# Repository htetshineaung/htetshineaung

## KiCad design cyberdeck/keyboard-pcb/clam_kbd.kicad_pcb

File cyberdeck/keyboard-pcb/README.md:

# Clamshell keyboard PCB (phase 2)

Our own thumb keyboard for the Pi 5 Clamshell: RP2040, 42 keys + mouse L/R (45 switches: the space bar has two) on 1.5 mm tactile
switches, a BlackBerry-style trackball breakout under a window in the board, OLED pads, battery voltage
sense. 4-layer (In1 solid GND plane,
In2 extra routing layer), 1.0 mm, 133 × 72 mm,
shaped to drop into the clamshell base under the deck.

| File | What it is |
|---|---|
| `circuit.py` | **Source of truth**: every part, value, MPN/LCSC, position and pin→net |
| `gen_sch.py` → `clam_kbd.kicad_sch` | KiCad 7 schematic (label-connected), opens in KiCad |
| `gen_pcb.py` → `clam_kbd.kicad_pcb`, `clam_kbd.dsn` | Placed PCB with nets, outline, GND pours; Specctra file for the autorouter |
| `verify_netlist.py` | Checks KiCad's exported netlist against `circuit.py`, pin by pin |
| `run_drc.py` | KiCad DRC through the pcbnew API |
| `gen_fab.py` → `fab/bom.csv`, `fab/cpl.csv` | JLCPCB assembly files (placements from `fab/routed_positions.csv`, the routed board's export) |
| `apply_tb_module.py`, `cluster_route.py`, `trim_dangling.py`, `tb_pipeline.sh` | Turn the routed rev A board into rev B (trackball breakout) without re-routing everything |
| `render/` | Top / bottom renders, schematic PDF |

```bash
python3 gen_sch.py && kicad-cli sch export netlist clam_kbd.kicad_sch -o clam_kbd.net && python3 verify_netlist.py
KICAD7_FOOTPRINT_DIR=/usr/share/kicad/footprints /usr/bin/python3 gen_pcb.py
/usr/bin/python3 run_drc.py drc.rpt
```

## Status
- Schematic: generated; KiCad netlist matches `circuit.py` on all 91 nets (0 mismatches).
- Placement: done, matched to the clamshell key mat; DRC clean apart from unrouted nets and
  cosmetic silkscreen overlaps.
- **Routing:** scripted pipeline, run with KiCad 10's Python on the Mac (KiCad 7 works too):
  1. `route_matrix.py clam_kbd.kicad_pcb clam_kbd_rN.kicad_pcb x.dsn`: clears old routing and
     pre-routes the regular key matrix (columns on top, rows on the bottom, locked).
  2. `stitch_gnd.py clam_kbd_rN.kicad_pcb clam_kbd_rN.kicad_pcb x.dsn`: one via per small-part
     GND pad, a 3x3 via grid in the RP2040 exposed pad, and the TESTEN stub.
  3. (the DSN written by step 2 is the autorouter input; `export_dsn.py` can hide the pours)
  4. `java -Djava.awt.headless=true -jar freerouting-2.5.0.jar --gui.enabled=false
     -de clam_kbd_rN.dsn -do clam_kbd_rN.ses -mp 60 -mt 6`
  5. Import the `.ses` (`pcbnew.ImportSpecctraSES`), then `stitch_gnd.py ... --grid` for a 3 mm
     stitching-via grid, then `kicad-cli pcb drc --refill-zones --save-board`.
  6. `fix_route.py board board U1.6 U1.7 --inner [--rip 0.6]`: grid router for any pins the
     autorouter leaves open (can rip up nearby tracks and reconnect them).
  7. `gnd_islands.py board.kicad_pcb` lists any ground islands; `export_jlc.sh board` gates on DRC and
     writes the Gerber zip.
  Result (rev A): 0 unconnected, 0 DRC errors, 1171 segments on F/In2/B, 215 vias.
  Rules (`clam_kbd_rN.kicad_pro`): 0.15 mm track and clearance, 0.5/0.3 mm vias, 0.3 mm to the
  edge; all within JLCPCB's standard 4-layer process (the router's few 0.09 mm neck-downs at the
  RP2040 pins are inside JLCPCB's 0.09 mm multilayer limit).
- **Trackball (rev B):** the ready-made BlackBerry-style trackball breakout (pins VCC GND BTN RHT
  LFT DWN UP WHT GRN RED BLU) sits *under* the board: its own 11-pin header is soldered through J6
  (plated holes, both boards), two M2 screws with 2.5 mm spacers (H6, H7) hold its other edge, and
  the ball comes up through a 14 × 14 mm window centred at (124, 44). The module's hall outputs and
  click go straight to the RP2040 and its RGB LED through 100 Ω R20–R22, on GPIOs chosen so the
  RP2040 pins come in the same top-to-bottom order as the header (GPIO20 click, 21 right, 22 left,
  23 down, 24 up, 27 / 28 / 29 LED G / R / B): the wires run as one straight bus. Each LED resistor
  sits level with its header pin. Either LED polarity works (the firmware picks it). WHT is not
  connected. The module runs from +3V3.
- **Rev B routing** (`tb_pipeline.sh`, on the Mac with KiCad 10): `apply_tb_module.py` removes the
  rev A hall sensors and their tracks, adds J6 / R20–R22 / H6–H7 / the window and clears copper they
  clash with (pad nets are checked against the generated board by hash); `fix_route.py` routes the
  new connections; `cluster_route.py` redoes the RP2040's right-side fan-out (pins 34–41 all need
  an escape now), trying routing orders until every pin gets out; `trim_dangling.py` cuts the
  stubs left over. Result: 0 unconnected, 0 DRC errors.

## Circuit
- **MCU:** RP2040 + W25Q16JVSSIQ 2 MB QSPI flash, 12 MHz ABM8-272-T3 crystal (15 pF, 1 kΩ on
  XOUT), BOOT button (QSPI_SS via 1 kΩ) and RESET, 100 nF per supply pin, 1 µF on VREG in/out.
- **Power:** +5 V from the battery step-down (J1) or the programming USB through a B5819W
  (so the Pi's 5 V never back-feeds a USB host) → AP2112K-3.3 LDO → +3V3 → RP2040 core LDO → +1V1.
- **Link to the Pi:** UART at 3.3 V on J1. In the clamshell the Pi's USB ports face out
  through the case wall, so the keyboard talks over the Pi 5's internal UART connector
  (`/dev/ttyAMA10`) and Linux turns key/mouse frames into a virtual keyboard and mouse.
- **Matrix:** 4 rows × 12 columns, 1N4148WS per key (cathode to row: rows driven low, columns
  pulled up). The space bar has two switches in parallel on one diode. L/R are on column 11.
- **I²C1** (GPIO18/19, 4.7 kΩ pull-ups): OLED (J2 pads).
- **Battery sense:** 100 kΩ / 33 kΩ divider + 100 nF on GPIO26 (8.4 V → 2.08 V).

| Connector | Pins | Goes to |
|---|---|---|
| J1 PI_LINK (JST-SH 4) | 1 +5V · 2 GND · 3 KB_RX · 4 KB_TX | step-down 5 V/GND; Pi 5 UART connector (Pi TX → KB_RX, Pi RX ← KB_TX, GND) |
| J5 USB_PROG (JST-SH 4) | 1 VBUS · 2 D− · 3 D+ · 4 GND | USB cable for flashing firmware (hold BOOT, tap RESET) |
| J4 VBAT (JST-SH 2) | 1 VBAT · 2 GND | 2S pack + (after the BMS) |
| J2 OLED (4 pads, 2.54 mm) | 1 GND · 2 VCC · 3 SCL · 4 SDA | 0.96" SSD1306 module, soldered flat. **Check your module's pin order** |

| RP2040 | Function | RP2040 | Function |
|---|---|---|---|
| GPIO0 / 1 | UART0 TX / RX → Pi | GPIO18 / 19 | I²C1 SDA / SCL |
| GPIO2–5 | ROW0–3 | GPIO20–24 | trackball click / right / left / down / up |
| GPIO6–17 | COL0–11 | GPIO25 | status LED |
| GPIO26 | battery sense (ADC0) | GPIO27 / 28 / 29 | trackball LED green / red / blue |

| J6 pin | 1 | 2 | 3 | 4 | 5 | 6 | 7 | 8 | 9 | 10 | 11 |
|---|---|---|---|---|---|---|---|---|---|---|---|
| Breakout | VCC | GND | BTN | RHT | LFT | DWN | UP | WHT | GRN | RED | BLU |
| Net | +3V3 | GND | TB_CLICK | TB_RIGHT | TB_LEFT | TB_DOWN | TB_UP | — | TB_LED_G | TB_LED_R | TB_LED_B |

## Before ordering
- Route, then re-run DRC and the netlist check.
- Confirm the LCSC numbers left blank (flash, crystal, JST-SH, KMR2) in JLCPCB's part search;
  JLCPCB can also match by MPN.
- Check part rotations in JLCPCB's placement preview (KiCad and JLCPCB zero-rotation
  conventions differ for some packages).
- Datasheet sites were not reachable from the build sandbox: pinouts were checked against the
  KiCad library symbols and the standard pin tables, not the PDFs.

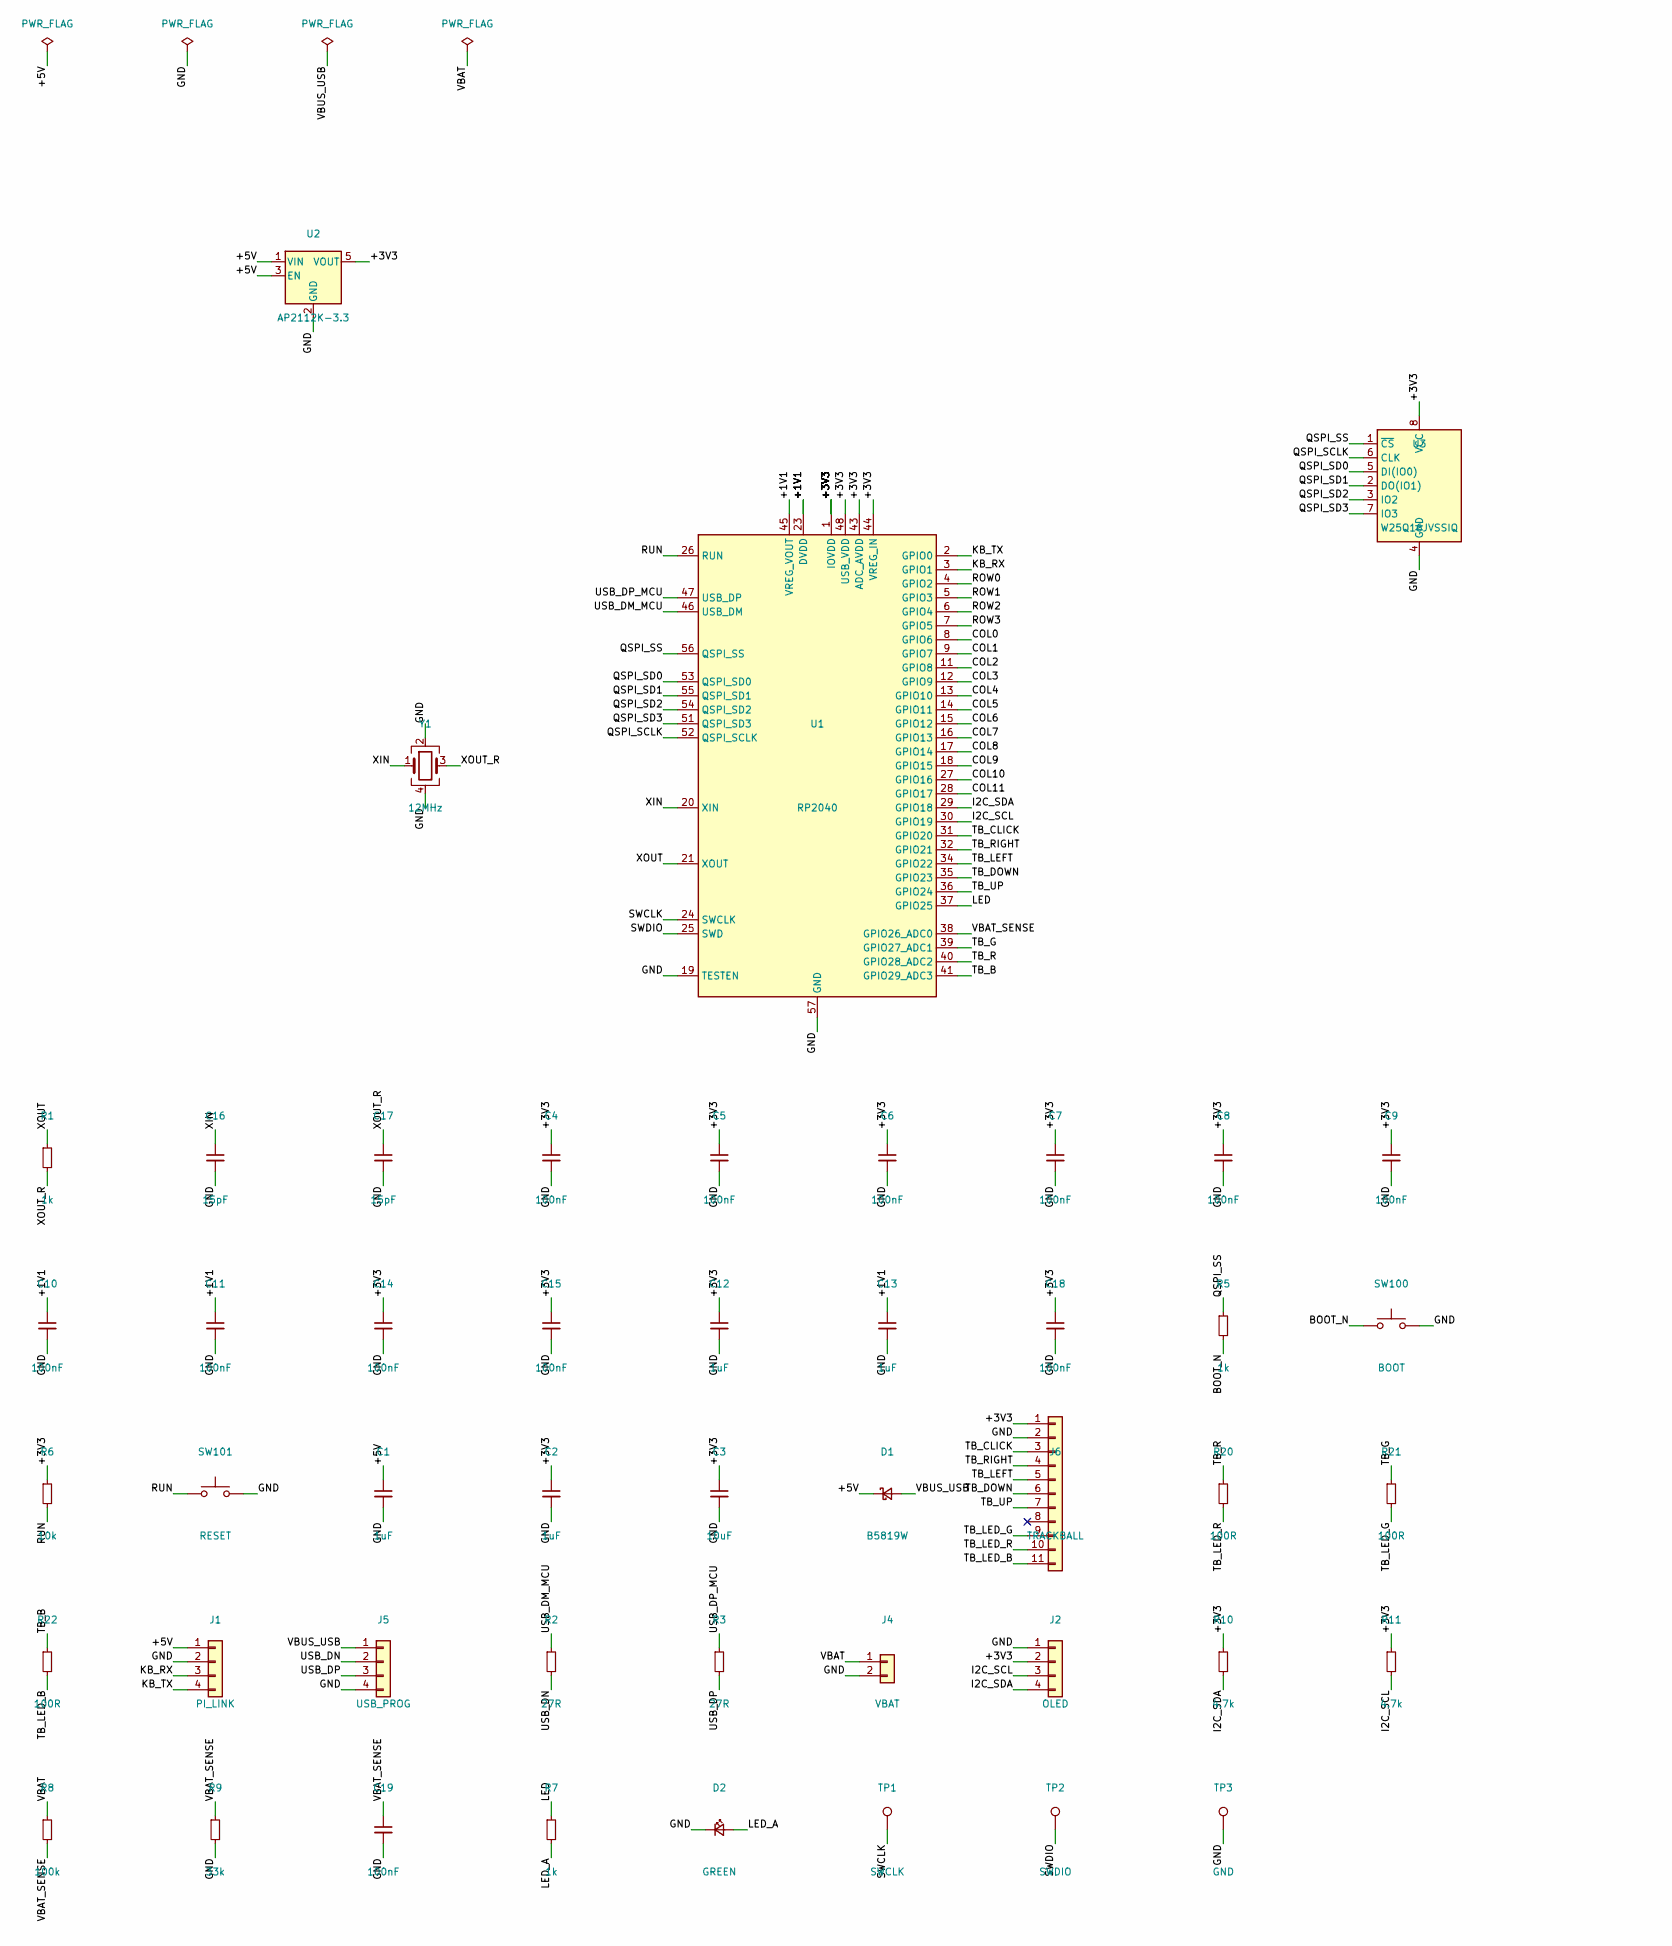
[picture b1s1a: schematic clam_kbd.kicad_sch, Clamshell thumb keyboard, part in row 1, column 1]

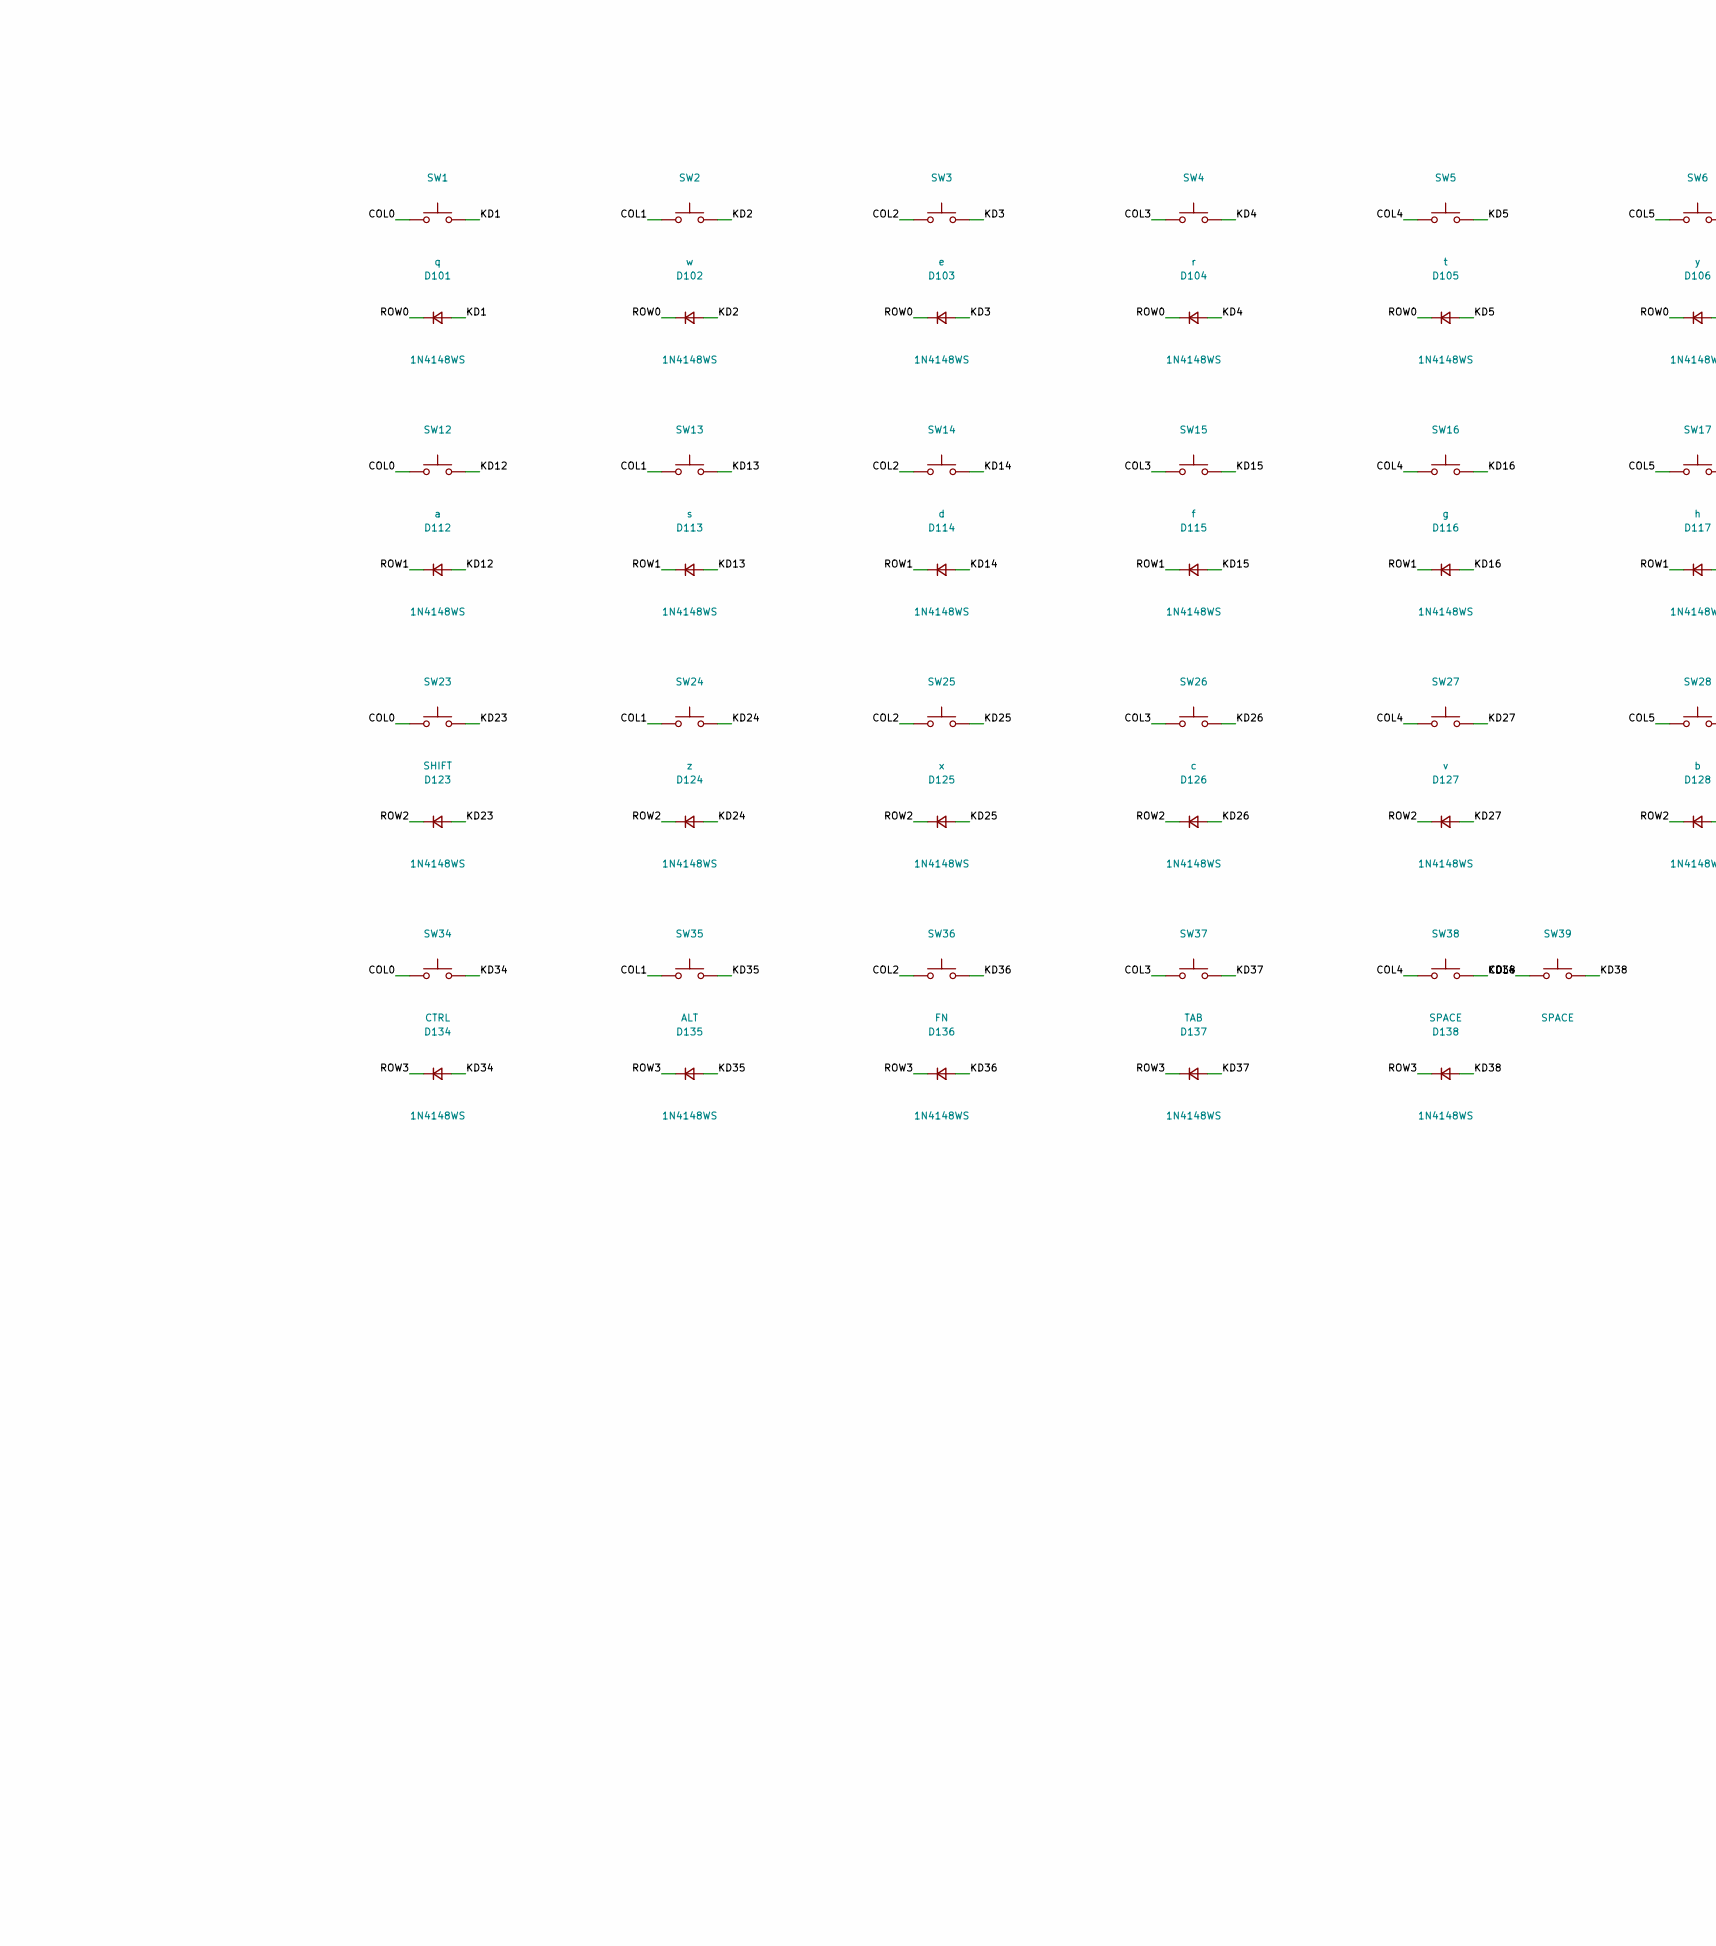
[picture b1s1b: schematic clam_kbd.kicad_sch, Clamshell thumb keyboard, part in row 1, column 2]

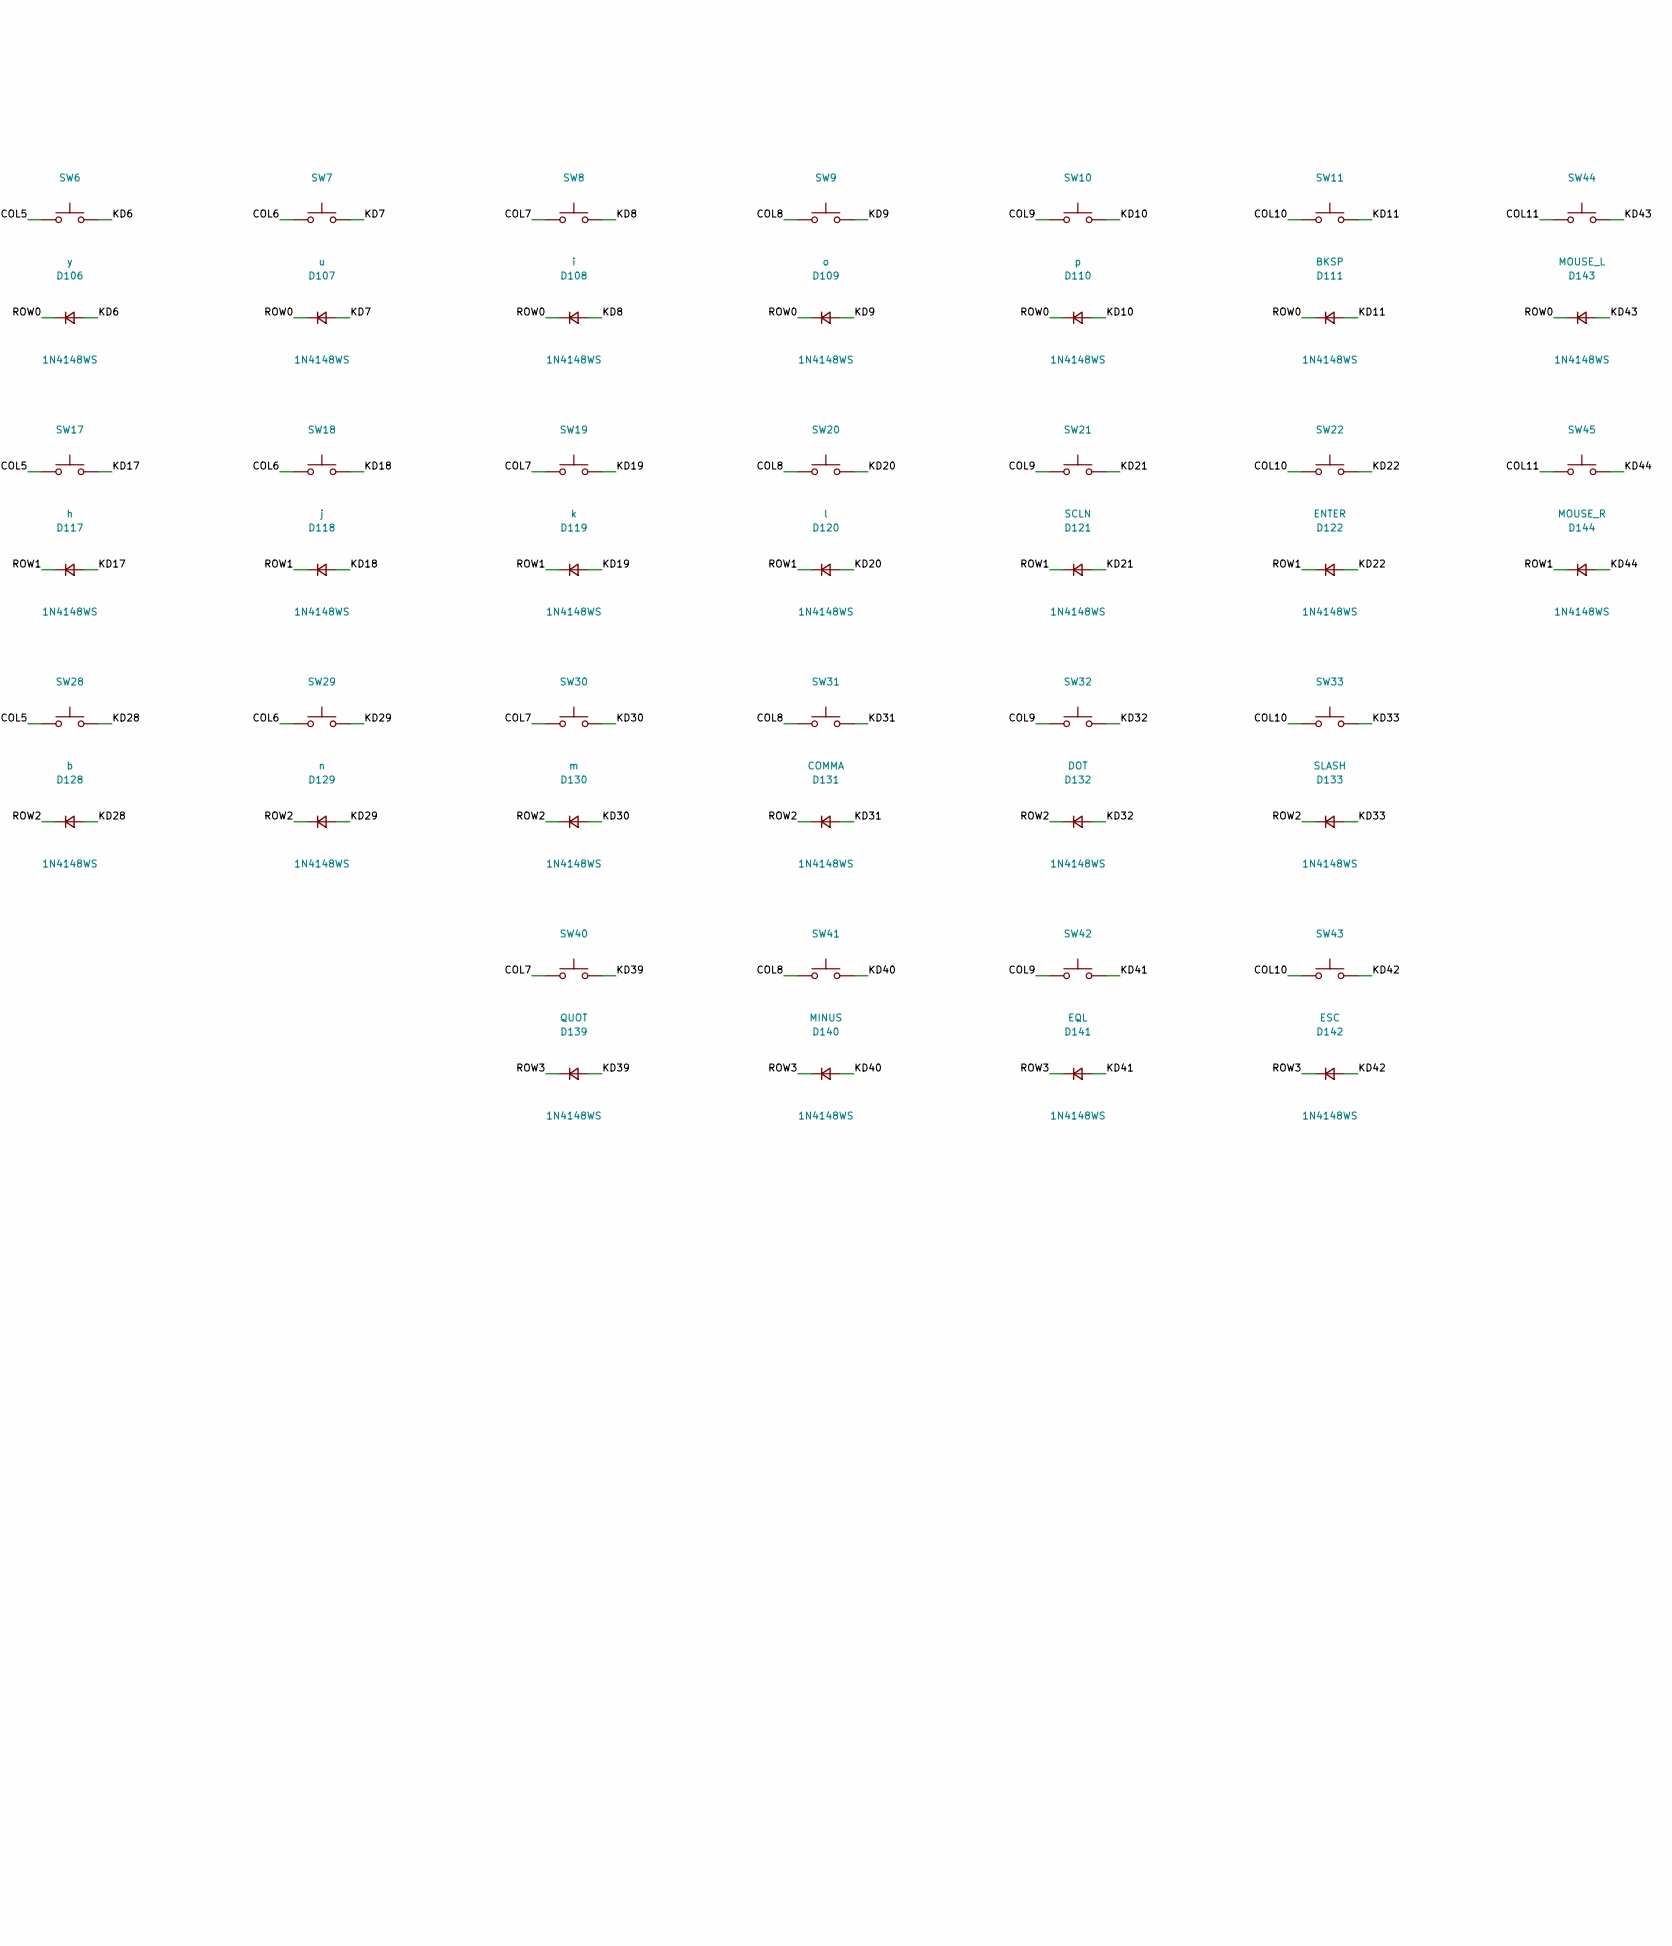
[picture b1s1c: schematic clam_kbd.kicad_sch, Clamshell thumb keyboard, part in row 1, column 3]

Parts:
C1, C2, C12, C13: 1uF; C_0402_1005Metric; MPN CL05A105KA5NQNC; LCSC C52923
C3: 10uF; C_0603_1608Metric; MPN CL10A106KP8NNNC; LCSC C19702
C4, C5, C6, C7, C8, C9, C10, C11, C14, C15, C18, C19: 100nF; C_0402_1005Metric; MPN CL05B104KO5NNNC; LCSC C1525
C16, C17: 15pF; C_0402_1005Metric; MPN 0402CG150J500NT; LCSC C1548
D1: B5819W; D_SOD-123; MPN B5819W; LCSC C8598
D2: GREEN; LED_0603_1608Metric; MPN KT-0603G; LCSC C72043
D101, D102, D103, D104, D105, D106, D107, D108, D109, D110, D111, D112, D113, D114, D115, D116, D117, D118, D119, D120, D121, D122, D123, D124, D125, D126, D127, D128, D129, D130, D131, D132, D133, D134, D135, D136, D137, D138, D139, D140, D141, D142, D143, D144: 1N4148WS; D_SOD-323; MPN 1N4148WS; LCSC C2128
J1: PI_LINK; JST_SH_SM04B-SRSS-TB_1x04-1MP_P1.00mm_Horizontal; MPN SM04B-SRSS-TB; LCSC C160404
J2: OLED; PinHeader_1x04_P2.54mm_Vertical; MPN SSD1306 0.96in 128x64 I2C module (GND V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
J4: VBAT; JST_SH_SM02B-SRSS-TB_1x02-1MP_P1.00mm_Horizontal; MPN SM02B-SRSS-TB; LCSC C160402
J5: USB_PROG; JST_SH_SM04B-SRSS-TB_1x04-1MP_P1.00mm_Horizontal; MPN SM04B-SRSS-TB; LCSC C160404
J6: TRACKBALL; PinHeader_1x11_P2.54mm_Vertical; MPN trackball breakout header (solder the m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
R1, R5, R7: 1k; R_0402_1005Metric; MPN 0402WGF1001TCE; LCSC C11702
R2, R3: 27R; R_0402_1005Metric; MPN 0402WGF270KTCE; LCSC C25100
R6: 10k; R_0402_1005Metric; MPN 0402WGF1002TCE; LCSC C25744
R8: 100k; R_0402_1005Metric; MPN 0402WGF1003TCE; LCSC C25741
R9: 33k; R_0402_1005Metric; MPN 0402WGF3302TCE; LCSC C25779
R10, R11: 4.7k; R_0402_1005Metric; MPN 0402WGF4701TCE; LCSC C25900
R20, R21, R22: 100R; R_0402_1005Metric; MPN 0402WGF1000TCE; LCSC C25076
SW1: q; SW_Push_1P1T_XKB_TS-1187A; MPN TS-1187A-B-A-B; LCSC C318884
SW2: w; SW_Push_1P1T_XKB_TS-1187A; MPN TS-1187A-B-A-B; LCSC C318884
SW3: e; SW_Push_1P1T_XKB_TS-1187A; MPN TS-1187A-B-A-B; LCSC C318884
SW4: r; SW_Push_1P1T_XKB_TS-1187A; MPN TS-1187A-B-A-B; LCSC C318884
SW5: t; SW_Push_1P1T_XKB_TS-1187A; MPN TS-1187A-B-A-B; LCSC C318884
SW6: y; SW_Push_1P1T_XKB_TS-1187A; MPN TS-1187A-B-A-B; LCSC C318884
SW7: u; SW_Push_1P1T_XKB_TS-1187A; MPN TS-1187A-B-A-B; LCSC C318884
SW8: i; SW_Push_1P1T_XKB_TS-1187A; MPN TS-1187A-B-A-B; LCSC C318884
SW9: o; SW_Push_1P1T_XKB_TS-1187A; MPN TS-1187A-B-A-B; LCSC C318884
SW10: p; SW_Push_1P1T_XKB_TS-1187A; MPN TS-1187A-B-A-B; LCSC C318884
SW11: BKSP; SW_Push_1P1T_XKB_TS-1187A; MPN TS-1187A-B-A-B; LCSC C318884
SW12: a; SW_Push_1P1T_XKB_TS-1187A; MPN TS-1187A-B-A-B; LCSC C318884
SW13: s; SW_Push_1P1T_XKB_TS-1187A; MPN TS-1187A-B-A-B; LCSC C318884
SW14: d; SW_Push_1P1T_XKB_TS-1187A; MPN TS-1187A-B-A-B; LCSC C318884
SW15: f; SW_Push_1P1T_XKB_TS-1187A; MPN TS-1187A-B-A-B; LCSC C318884
SW16: g; SW_Push_1P1T_XKB_TS-1187A; MPN TS-1187A-B-A-B; LCSC C318884
SW17: h; SW_Push_1P1T_XKB_TS-1187A; MPN TS-1187A-B-A-B; LCSC C318884
SW18: j; SW_Push_1P1T_XKB_TS-1187A; MPN TS-1187A-B-A-B; LCSC C318884
SW19: k; SW_Push_1P1T_XKB_TS-1187A; MPN TS-1187A-B-A-B; LCSC C318884
SW20: l; SW_Push_1P1T_XKB_TS-1187A; MPN TS-1187A-B-A-B; LCSC C318884
SW21: SCLN; SW_Push_1P1T_XKB_TS-1187A; MPN TS-1187A-B-A-B; LCSC C318884
SW22: ENTER; SW_Push_1P1T_XKB_TS-1187A; MPN TS-1187A-B-A-B; LCSC C318884
SW23: SHIFT; SW_Push_1P1T_XKB_TS-1187A; MPN TS-1187A-B-A-B; LCSC C318884
SW24: z; SW_Push_1P1T_XKB_TS-1187A; MPN TS-1187A-B-A-B; LCSC C318884
SW25: x; SW_Push_1P1T_XKB_TS-1187A; MPN TS-1187A-B-A-B; LCSC C318884
SW26: c; SW_Push_1P1T_XKB_TS-1187A; MPN TS-1187A-B-A-B; LCSC C318884
SW27: v; SW_Push_1P1T_XKB_TS-1187A; MPN TS-1187A-B-A-B; LCSC C318884
SW28: b; SW_Push_1P1T_XKB_TS-1187A; MPN TS-1187A-B-A-B; LCSC C318884
SW29: n; SW_Push_1P1T_XKB_TS-1187A; MPN TS-1187A-B-A-B; LCSC C318884
SW30: m; SW_Push_1P1T_XKB_TS-1187A; MPN TS-1187A-B-A-B; LCSC C318884
SW31: COMMA; SW_Push_1P1T_XKB_TS-1187A; MPN TS-1187A-B-A-B; LCSC C318884
SW32: DOT; SW_Push_1P1T_XKB_TS-1187A; MPN TS-1187A-B-A-B; LCSC C318884
SW33: SLASH; SW_Push_1P1T_XKB_TS-1187A; MPN TS-1187A-B-A-B; LCSC C318884
SW34: CTRL; SW_Push_1P1T_XKB_TS-1187A; MPN TS-1187A-B-A-B; LCSC C318884
SW35: ALT; SW_Push_1P1T_XKB_TS-1187A; MPN TS-1187A-B-A-B; LCSC C318884
SW36: FN; SW_Push_1P1T_XKB_TS-1187A; MPN TS-1187A-B-A-B; LCSC C318884
SW37: TAB; SW_Push_1P1T_XKB_TS-1187A; MPN TS-1187A-B-A-B; LCSC C318884
SW38, SW39: SPACE; SW_Push_1P1T_XKB_TS-1187A; MPN TS-1187A-B-A-B; LCSC C318884
SW40: QUOT; SW_Push_1P1T_XKB_TS-1187A; MPN TS-1187A-B-A-B; LCSC C318884
SW41: MINUS; SW_Push_1P1T_XKB_TS-1187A; MPN TS-1187A-B-A-B; LCSC C318884
SW42: EQL; SW_Push_1P1T_XKB_TS-1187A; MPN TS-1187A-B-A-B; LCSC C318884
SW43: ESC; SW_Push_1P1T_XKB_TS-1187A; MPN TS-1187A-B-A-B; LCSC C318884
SW44: MOUSE_L; SW_Push_1P1T_XKB_TS-1187A; MPN TS-1187A-B-A-B; LCSC C318884
SW45: MOUSE_R; SW_Push_1P1T_XKB_TS-1187A; MPN TS-1187A-B-A-B; LCSC C318884
SW100: BOOT; SW_Push_1P1T_NO_CK_KMR2; MPN KMR221GLFS; LCSC C72443
SW101: RESET; SW_Push_1P1T_NO_CK_KMR2; MPN KMR221GLFS; LCSC C72443
TP1: SWCLK; TestPoint_Pad_D1.0mm
TP2: SWDIO; TestPoint_Pad_D1.0mm
TP3: GND; TestPoint_Pad_D1.0mm
U1: RP2040; QFN-56-1EP_7x7mm_P0.4mm_EP3.2x3.2mm; MPN RP2040; LCSC C2040
U2: AP2112K-3.3; SOT-23-5; MPN AP2112K-3.3TRG1; LCSC C51118
U3: W25Q16JVSSIQ; SOIC-8_5.23x5.23mm_P1.27mm; MPN W25Q16JVSSIQ; LCSC C131025
Y1: 12MHz; Crystal_SMD_3225-4Pin_3.2x2.5mm; MPN ABM8-272-T3; LCSC C20625731

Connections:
+1V1: C10.1, C11.1, C13.1, U1.23 (DVDD), U1.45 (VREG_VOUT), U1.50 (DVDD)
+3V3: C2.1, C3.1, C4.1, C5.1, C6.1, C7.1, C8.1, C9.1, C12.1, C14.1, C15.1, C18.1, J2.2, J6.1, R6.1, R10.1, R11.1, U1.1 (IOVDD), U1.10 (IOVDD), U1.22 (IOVDD), U1.33 (IOVDD), U1.42 (IOVDD), U1.43 (ADC_AVDD), U1.44 (VREG_IN), U1.48 (USB_VDD), U1.49 (IOVDD), U2.5 (VOUT), U3.8 (VCC)
+5V: C1.1, D1.1 (K), J1.1, U2.1 (VIN), U2.3 (EN)
BOOT_N: R5.2, SW100.1
COL0: SW1.1, SW12.1, SW23.1, SW34.1, U1.8 (GPIO6)
COL1: SW2.1, SW13.1, SW24.1, SW35.1, U1.9 (GPIO7)
COL2: SW3.1, SW14.1, SW25.1, SW36.1, U1.11 (GPIO8)
COL3: SW4.1, SW15.1, SW26.1, SW37.1, U1.12 (GPIO9)
COL4: SW5.1, SW16.1, SW27.1, SW38.1, SW39.1, U1.13 (GPIO10)
COL5: SW6.1, SW17.1, SW28.1, U1.14 (GPIO11)
COL6: SW7.1, SW18.1, SW29.1, U1.15 (GPIO12)
COL7: SW8.1, SW19.1, SW30.1, SW40.1, U1.16 (GPIO13)
COL8: SW9.1, SW20.1, SW31.1, SW41.1, U1.17 (GPIO14)
COL9: SW10.1, SW21.1, SW32.1, SW42.1, U1.18 (GPIO15)
COL10: SW11.1, SW22.1, SW33.1, SW43.1, U1.27 (GPIO16)
COL11: SW44.1, SW45.1, U1.28 (GPIO17)
GND: C1.2, C2.2, C3.2, C4.2, C5.2, C6.2, C7.2, C8.2, C9.2, C10.2, C11.2, C12.2, C13.2, C14.2, C15.2, C16.2, C17.2, C18.2, C19.2, D2.1 (K), J1.2, J2.1, J4.2, J5.4, J6.2, R9.2, SW100.2, SW101.2, TP3.1, U1.19 (TESTEN), U1.57 (GND), U2.2 (GND), U3.4 (GND), Y1.2, Y1.4
I2C_SCL: J2.3, R11.2, U1.30 (GPIO19)
I2C_SDA: J2.4, R10.2, U1.29 (GPIO18)
KB_RX: J1.3, U1.3 (GPIO1)
KB_TX: J1.4, U1.2 (GPIO0)
KD1: D101.2 (A), SW1.2
KD2: D102.2 (A), SW2.2
KD3: D103.2 (A), SW3.2
KD4: D104.2 (A), SW4.2
KD5: D105.2 (A), SW5.2
KD6: D106.2 (A), SW6.2
KD7: D107.2 (A), SW7.2
KD8: D108.2 (A), SW8.2
KD9: D109.2 (A), SW9.2
KD10: D110.2 (A), SW10.2
KD11: D111.2 (A), SW11.2
KD12: D112.2 (A), SW12.2
KD13: D113.2 (A), SW13.2
KD14: D114.2 (A), SW14.2
KD15: D115.2 (A), SW15.2
KD16: D116.2 (A), SW16.2
KD17: D117.2 (A), SW17.2
KD18: D118.2 (A), SW18.2
KD19: D119.2 (A), SW19.2
KD20: D120.2 (A), SW20.2
KD21: D121.2 (A), SW21.2
KD22: D122.2 (A), SW22.2
KD23: D123.2 (A), SW23.2
KD24: D124.2 (A), SW24.2
KD25: D125.2 (A), SW25.2
KD26: D126.2 (A), SW26.2
KD27: D127.2 (A), SW27.2
KD28: D128.2 (A), SW28.2
KD29: D129.2 (A), SW29.2
KD30: D130.2 (A), SW30.2
KD31: D131.2 (A), SW31.2
KD32: D132.2 (A), SW32.2
KD33: D133.2 (A), SW33.2
KD34: D134.2 (A), SW34.2
KD35: D135.2 (A), SW35.2
KD36: D136.2 (A), SW36.2
KD37: D137.2 (A), SW37.2
KD38: D138.2 (A), SW38.2, SW39.2
KD39: D139.2 (A), SW40.2
KD40: D140.2 (A), SW41.2
KD41: D141.2 (A), SW42.2
KD42: D142.2 (A), SW43.2
KD43: D143.2 (A), SW44.2
KD44: D144.2 (A), SW45.2
LED: R7.1, U1.37 (GPIO25)
LED_A: D2.2 (A), R7.2
QSPI_SCLK: U1.52 (QSPI_SCLK), U3.6 (CLK)
QSPI_SD0: U1.53 (QSPI_SD0), U3.5 (DI(IO0))
QSPI_SD1: U1.55 (QSPI_SD1), U3.2 (DO(IO1))
QSPI_SD2: U1.54 (QSPI_SD2), U3.3 (IO2)
QSPI_SD3: U1.51 (QSPI_SD3), U3.7 (IO3)
QSPI_SS: R5.1, U1.56 (QSPI_SS), U3.1 (~CS)
ROW0: D101.1 (K), D102.1 (K), D103.1 (K), D104.1 (K), D105.1 (K), D106.1 (K), D107.1 (K), D108.1 (K), D109.1 (K), D110.1 (K), D111.1 (K), D143.1 (K), U1.4 (GPIO2)
ROW1: D112.1 (K), D113.1 (K), D114.1 (K), D115.1 (K), D116.1 (K), D117.1 (K), D118.1 (K), D119.1 (K), D120.1 (K), D121.1 (K), D122.1 (K), D144.1 (K), U1.5 (GPIO3)
ROW2: D123.1 (K), D124.1 (K), D125.1 (K), D126.1 (K), D127.1 (K), D128.1 (K), D129.1 (K), D130.1 (K), D131.1 (K), D132.1 (K), D133.1 (K), U1.6 (GPIO4)
ROW3: D134.1 (K), D135.1 (K), D136.1 (K), D137.1 (K), D138.1 (K), D139.1 (K), D140.1 (K), D141.1 (K), D142.1 (K), U1.7 (GPIO5)
RUN: R6.2, SW101.1, U1.26 (RUN)
SWCLK: TP1.1, U1.24 (SWCLK)
SWDIO: TP2.1, U1.25 (SWD)
TB_B: R22.1, U1.41 (GPIO29_ADC3)
TB_CLICK: J6.3, U1.31 (GPIO20)
TB_DOWN: J6.6, U1.35 (GPIO23)
TB_G: R21.1, U1.39 (GPIO27_ADC1)
TB_LED_B: J6.11, R22.2
TB_LED_G: J6.9, R21.2
TB_LED_R: J6.10, R20.2
TB_LEFT: J6.5, U1.34 (GPIO22)
TB_R: R20.1, U1.40 (GPIO28_ADC2)
TB_RIGHT: J6.4, U1.32 (GPIO21)
TB_UP: J6.7, U1.36 (GPIO24)
USB_DM_MCU: R2.1, U1.46 (USB_DM)
USB_DN: J5.2, R2.2
USB_DP: J5.3, R3.2
USB_DP_MCU: R3.1, U1.47 (USB_DP)
VBAT: J4.1, R8.1
VBAT_SENSE: C19.1, R8.2, R9.1, U1.38 (GPIO26_ADC0)
VBUS_USB: D1.2 (A), J5.1
XIN: C16.1, U1.20 (XIN), Y1.1
XOUT: R1.1, U1.21 (XOUT)
XOUT_R: C17.1, R1.2, Y1.3

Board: 4 copper layers, 144 parts (86 on the bottom side), 101 nets, no tracks yet.

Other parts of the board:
H1, H2, H3, H4, H5, H6, H7: MountingHole_2.2mm_M2

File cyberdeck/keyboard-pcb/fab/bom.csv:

Comment,Designator,Footprint,LCSC,MPN,Qty
Key switch 5.1x5.1x1.5,"SW1,SW2,SW3,SW4,SW5,SW6,SW7,SW8,SW9,SW10,SW11,SW12,SW13,SW14,SW15,SW16,SW17,SW18,SW19,SW20,SW21,SW22,SW23,SW24,SW25,SW26,SW27,SW28,SW29,SW30,SW31,SW32,SW33,SW34,SW35,SW36,SW37,SW38,SW39,SW40,SW41,SW42,SW43,SW44,SW45",SW_Push_1P1T_XKB_TS-1187A,C318884,TS-1187A-B-A-B,45
BOOT,SW100,SW_Push_1P1T_NO_CK_KMR2,C72443,KMR221GLFS,1
RESET,SW101,SW_Push_1P1T_NO_CK_KMR2,C72443,KMR221GLFS,1
1k,"R1,R5,R7",R_0402_1005Metric,C11702,0402WGF1001TCE,3
GREEN,D2,LED_0603_1608Metric,C72043,KT-0603G,1
100nF,"C4,C5,C6,C7,C8,C9,C10,C11,C14,C15,C18,C19",C_0402_1005Metric,C1525,CL05B104KO5NNNC,12
1N4148WS,"D101,D102,D103,D104,D105,D106,D107,D108,D109,D110,D111,D112,D113,D114,D115,D116,D117,D118,D119,D120,D121,D122,D123,D124,D125,D126,D127,D128,D129,D130,D131,D132,D133,D134,D135,D136,D137,D138,D139,D140,D141,D142,D143,D144",D_SOD-323,C2128,1N4148WS,44
AP2112K-3.3,U2,SOT-23-5,C51118,AP2112K-3.3TRG1,1
100R,"R20,R21,R22",R_0402_1005Metric,C25076,0402WGF1000TCE,3
USB_PROG,J5,JST_SH_SM04B-SRSS-TB_1x04-1MP_P1.00mm_Horizontal,C160404,SM04B-SRSS-TB,1
100k,R8,R_0402_1005Metric,C25741,0402WGF1003TCE,1
4.7k,"R10,R11",R_0402_1005Metric,C25900,0402WGF4701TCE,2
PI_LINK,J1,JST_SH_SM04B-SRSS-TB_1x04-1MP_P1.00mm_Horizontal,C160404,SM04B-SRSS-TB,1
33k,R9,R_0402_1005Metric,C25779,0402WGF3302TCE,1
1uF,"C1,C2,C12,C13",C_0402_1005Metric,C52923,CL05A105KA5NQNC,4
27R,"R2,R3",R_0402_1005Metric,C25100,0402WGF270KTCE,2
12MHz,Y1,Crystal_SMD_3225-4Pin_3.2x2.5mm,C20625731,ABM8-272-T3,1
B5819W,D1,D_SOD-123,C8598,B5819W,1
10k,R6,R_0402_1005Metric,C25744,0402WGF1002TCE,1
RP2040,U1,QFN-56-1EP_7x7mm_P0.4mm_EP3.2x3.2mm,C2040,RP2040,1
W25Q16JVSSIQ,U3,SOIC-8_5.23x5.23mm_P1.27mm,C131025,W25Q16JVSSIQ,1
15pF,"C16,C17",C_0402_1005Metric,C1548,0402CG150J500NT,2
10uF,C3,C_0603_1608Metric,C19702,CL10A106KP8NNNC,1
VBAT,J4,JST_SH_SM02B-SRSS-TB_1x02-1MP_P1.00mm_Horizontal,C160402,SM02B-SRSS-TB,1

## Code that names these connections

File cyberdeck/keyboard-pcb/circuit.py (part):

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      "24": "SWCLK", "25": "SWDIO", "26": "RUN",
      "46": "USB_DM_MCU", "47": "USB_DP_MCU",
      "51": "QSPI_SD3", "52": "QSPI_SCLK", "53": "QSPI_SD0", "54": "QSPI_SD2", "55": "QSPI_SD1", "56": "QSPI_SS",
      "2": "KB_TX", "3": "KB_RX",                       # GPIO0/1 = UART0 TX/RX -> Pi
      "4": "ROW0", "5": "ROW1", "6": "ROW2", "7": "ROW3",                # GPIO2..5
      "8": "COL0", "9": "COL1", "11": "COL2", "12": "COL3", "13": "COL4", "14": "COL5",  # GPIO6..11
      "15": "COL6", "16": "COL7", "17": "COL8", "18": "COL9", "27": "COL10", "28": "COL11",  # GPIO12..17
      "29": "I2C_SDA", "30": "I2C_SCL",                 # GPIO18/19 = I2C1
      # trackball: pins in the same top-to-bottom order as the breakout header, so the wires run as
      # one straight bus: GPIO20 click, 21 right, 22 left, 23 down, 24 up, 27 / 28 / 29 LED G / R / B
      "31": "TB_CLICK", "32": "TB_RIGHT", "34": "TB_LEFT", "35": "TB_DOWN", "36": "TB_UP",
      "39": "TB_G", "40": "TB_R", "41": "TB_B",
      "37": "LED",                                      # GPIO25
      "38": "VBAT_SENSE",                               # GPIO26 / ADC0
      }
part("U1", "MCU_RaspberryPi:RP2040", "Package_DFN_QFN:QFN-56-1EP_7x7mm_P0.4mm_EP3.2x3.2mm", "RP2040", rp,
     (MX, MY), mpn="RP2040", lcsc="C2040")
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                   "7": "TB_UP", "9": "TB_LED_G", "10": "TB_LED_R", "11": "TB_LED_B"},
     (TB_PIN_X, TB_VCC_Y), side="top", mpn="trackball breakout header (solder the module's pins through)",
     dnp=True)
for i, (col, gpio_net, pin) in enumerate((("R", "TB_R", 10), ("G", "TB_G", 9), ("B", "TB_B", 11))):
    # each LED resistor sits level with its header pin: a short straight link
    part(f"R{20 + i}", "Device:R_Small", R0402, "100R", {"1": gpio_net, "2": f"TB_LED_{col}"},
         (TB_PIN_X - 4.3, TB_VCC_Y - 2.54 * (pin - 1)), rot=0, mpn="0402WGF1000TCE", lcsc="C25076")
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part("J4", "Connector_Generic:Conn_01x02", "Connector_JST:JST_SH_SM02B-SRSS-TB_1x02-1MP_P1.00mm_Horizontal", "VBAT",
     {"1": "VBAT", "2": "GND"}, (108.5, 24.0), mpn="SM02B-SRSS-TB", lcsc="C160402")
part("J2", "Connector_Generic:Conn_01x04", "Connector_PinHeader_2.54mm:PinHeader_1x04_P2.54mm_Vertical", "OLED",
     {"1": "GND", "2": "+3V3", "3": "I2C_SCL", "4": "I2C_SDA"}, (OLED_CX - 3.81, 68.3), side="top", rot=90,
     mpn="SSD1306 0.96in 128x64 I2C module (GND VCC SCL SDA)")

# --- I2C pull-ups, battery sense, status LED, SWD pads
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
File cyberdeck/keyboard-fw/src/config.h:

// Clamshell keyboard firmware - pins and tunables.
// Pin numbers are RP2040 GPIOs and match cyberdeck/keyboard-pcb/circuit.py.
#pragma once

// --- link to the Pi 5 (J1 PI_LINK -> Pi 5 3-pin debug UART, /dev/ttyAMA10)
#define PIN_LINK_TX      0          // KB_TX -> Pi RX
#define PIN_LINK_RX      1          // KB_RX <- Pi TX
#define LINK_BAUD        115200

// --- key matrix: rows are driven low one at a time, columns read with pull-ups
//     (diodes: anode at the switch, cathode at the row)
#define PIN_ROW0         2          // ROW0..ROW3 = GPIO2..5
#define PIN_COL0         6          // COL0..COL11 = GPIO6..17
#define MATRIX_ROWS      4
#define MATRIX_COLS      12
#define DEBOUNCE_MS      5

// --- OLED (I2C1)
#define PIN_I2C_SDA      18
#define PIN_I2C_SCL      19
#define OLED_ADDR        0x3C
#define OLED_SH1106      0          // 1 if your 0.96" module uses the SH1106 controller (132 columns)
#define OLED_FLIP        0          // 1 to rotate the picture 180 degrees

// --- trackball breakout (J6): each roller's hall sensor toggles its pin once per magnet pass;
//     BTN pulls low when the ball is pressed. GPIO order matches the header so the PCB bus is straight.
#define PIN_TB_CLICK     20
#define PIN_TB_RIGHT     21
#define PIN_TB_LEFT      22
#define PIN_TB_DOWN      23
#define PIN_TB_UP        24
// its RGB backlight, through 100R each; set TB_LED_ACTIVE_LOW to 0 if yours lights when driven high
#define PIN_TB_LED_G     27
#define PIN_TB_LED_R     28
#define PIN_TB_LED_B     29
#define TB_LED_ACTIVE_LOW 1
#define TB_PERIOD_MS     8          // motion report period
#define TB_GAIN          3.0f       // pointer counts per hall edge at slow speed
#define TB_ACCEL         0.35f      // extra gain per edge/period of speed
#define TB_MAX_FACTOR    14.0f
#define TB_SCROLL_DIV    4          // hall edges per wheel notch while fn is held

// --- misc
#define PIN_LED          25         // status LED (caps lock)
#define PIN_VBAT_ADC     26         // ADC0: VBAT through 100k / 33k
#define VBAT_DIV_NUM     133        // Vbat = Vadc * 133 / 33
#define VBAT_DIV_DEN     33
#define ADC_VREF_MV      3300

#define LINK_TIMEOUT_MS  6000       // no PING from the Pi for this long -> "Pi offline"
#define FW_VERSION_MAJOR 1
#define FW_VERSION_MINOR 0
